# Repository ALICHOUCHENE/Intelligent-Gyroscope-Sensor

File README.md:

# Intelligent-Gyroscope-Sensor

Intelligent gyroscope sensor for Electronic stability control

Recognizing how a vehicle is steered and then alerting drivers in real time is of utmost importance to the vehicle and driver’s safety, since fatal accidents are often caused by dangerous vehicle maneuvers, such as rapid turns, fast lane-changes, etc.
In this paper, we make use of an intelligent sensor to take one step forward by developing a real-time accurate recognition system for dangerous vehicle steering maneuvers without the driver’s involvement. 
The basic idea is to use the sensor data to capture differences in the vehicle’s angular speed due to vehicle steering maneuvers, including turns, lane-changes and U-turns. 

 **Here the features of the Sensor :**

- STM32F103C8T6 ARM 32-bit Cortex™-M3 is the CPU of the board. Higher frequency, higher speed and cost-effictive.

- Gyroscope module, MPU6050, with I2C communication protocol. 

- CAN transeiver SN65HVD230

- SWD programming Interface.

- SPI for serial communication.

- USART for AT-commands mode in order to test the sensor before embedded it in the CAN bus.

- Voltage regulator with reverse voltage protection circuit.

**The schematic of the board :**

**The PCB layout of the board :**

**Board View :**

# Manufacturing : 

After finishing the Routing and verifying the pcb. We will make the board at JLC PCB and we chose also the PCB Assembly service.
Here is the BOM and posistion file needed to order from JLC PCB :

**BOM :**

| Designator | Value         | Footprint                                                 | LCSC Part |
|------------|---------------|-----------------------------------------------------------|-----------|
| C1         | 100nF         | Capacitor_SMD:C_0805_2012Metric_Pad1.15x1.40mm_HandSolder | C49678    |
| C2         | 10nF          | Capacitor_SMD:C_0402_1005Metric                           | C1525     |
| C3         | 100nF         | Capacitor_SMD:C_0402_1005Metric                           | C1525     |
| C4         | 100nF         | Capacitor_SMD:C_0402_1005Metric                           | C1525     |
| C5         | 100nF         | Capacitor_SMD:C_0402_1005Metric                           | C1525     |
| C6         | 100nF         | Capacitor_SMD:C_0402_1005Metric                           | C1525     |
| C7         | 100nF         | Capacitor_SMD:C_0402_1005Metric                           | C1525     |
| C8         | 100nF         | Capacitor_SMD:C_0402_1005Metric                           | C1525     |
| C12        | 100nF         | Capacitor_SMD:C_0402_1005Metric                           | C1525     |
| C13        | 100nF         | Capacitor_SMD:C_0402_1005Metric                           | C1525     |
| C15        | 100nF         | Capacitor_SMD:C_0402_1005Metric                           | C1525     |
| C16        | 100nF         | Capacitor_SMD:C_0402_1005Metric                           | C1525     |
| C9         | 4.7uF         | Capacitor_SMD:C_0402_1005Metric                           | C23733    |
| C10        | 4.7uF         | Capacitor_SMD:C_0402_1005Metric                           | C23733    |
| C11        | 4.7uF         | Capacitor_SMD:C_0402_1005Metric                           | C23733    |
| C14        | 2.2uF         | Capacitor_SMD:C_0402_1005Metric                           | C12530    |
| C17        | 470nF         | Capacitor_Tantalum_SMD:CP_EIA-2012-12_Kemet-R             |           |
| C18        | 22pF          | Capacitor_SMD:C_0402_1005Metric                           | C70464    |
| C19        | 22pF          | Capacitor_SMD:C_0402_1005Metric                           | C70464    |
| D1         | LED           | LED_SMD:LED_0402_1005Metric                               | C71911    |
| D2         | LED           | LED_SMD:LED_0402_1005Metric                               | C71911    |
| Q1         | AO3401A       | Package_TO_SOT_SMD:SOT-23                                 | C15127    |
| R1         | 4.7K          | Resistor_SMD:R_0402_1005Metric                            | C25900    |
| R2         | 4.7K          | Resistor_SMD:R_0402_1005Metric                            | C25900    |
| R3         | 100K          | Resistor_SMD:R_0402_1005Metric                            | C25741    |
| R4         | 1K            | Resistor_SMD:R_0402_1005Metric                            | C11702    |
| R5         | 1K            | Resistor_SMD:R_0402_1005Metric                            | C11702    |
| R6         | 10k           | Resistor_SMD:R_0402_1005Metric                            | C25744    |
| R7         | 1M            | Resistor_SMD:R_0402_1005Metric                            | C26083    |
| U1         | AMS1117-3.3   | Package_TO_SOT_SMD:SOT-223-3_TabPin2                      | C6186     |
| U2         | STM32F103C8Tx | Package_QFP:LQFP-48_7x7mm_P0.5mm                          | C8734     |
| U3         | MPU-6050      | Sensor_Motion:InvenSense_QFN-24_4x4mm_P0.5mm              | C24112    |
| U4         | SN65HVD230    | Package_SO:SOIC-8_3.9x4.9mm_P1.27mm                       | C12084    |
| Y1         | 8MHz          | Crystal:Crystal_SMD_0603-2Pin_6.0x3.5mm                   | C111120   |

**Position file :**

| Designator | Value         | Footprint                                   | Mid X      | Mid Y       | Rotation   | Layer |
|------------|---------------|---------------------------------------------|------------|-------------|------------|-------|
| C1         | 100nF         | C_0805_2012Metric_Pad1.15x1.40mm_HandSolder | 106.680000 | -76.708000  | 0.000000   | top   |
| C2         | 10nF          | C_0402_1005Metric                           | 105.156000 | -85.090000  | 0.000000   | top   |
| C3         | 100nF         | C_0402_1005Metric                           | 107.188000 | -85.344000  | 90.000000  | top   |
| C4         | 100nF         | C_0402_1005Metric                           | 119.126000 | -84.074000  | 180.000000 | top   |
| C5         | 100nF         | C_0402_1005Metric                           | 108.458000 | -85.344000  | 270.000000 | top   |
| C6         | 100nF         | C_0402_1005Metric                           | 120.142000 | -95.250000  | 90.000000  | top   |
| C7         | 100nF         | C_0402_1005Metric                           | 105.664000 | -95.758000  | 270.000000 | top   |
| C8         | 100nF         | C_0402_1005Metric                           | 119.126000 | -85.090000  | 180.000000 | top   |
| C9         | 4.7uF         | C_0402_1005Metric                           | 119.126000 | -95.250000  | 90.000000  | top   |
| C10        | 4.7uF         | C_0402_1005Metric                           | 104.648000 | -95.758000  | 270.000000 | top   |
| C11        | 4.7uF         | C_0402_1005Metric                           | 119.126000 | -86.106000  | 180.000000 | top   |
| C12        | 100nF         | C_0402_1005Metric                           | 100.584000 | -87.376000  | 90.000000  | top   |
| C13        | 100nF         | C_0402_1005Metric                           | 103.124000 | -85.090000  | 180.000000 | top   |
| C14        | 2.2uF         | C_0402_1005Metric                           | 102.616000 | -92.456000  | 180.000000 | top   |
| C15        | 100nF         | C_0402_1005Metric                           | 121.920000 | -95.250000  | 90.000000  | top   |
| C16        | 100nF         | C_0402_1005Metric                           | 107.188000 | -102.870000 | 180.000000 | top   |
| C17        | 470nF         | CP_EIA-2012-12_Kemet-R                      | 123.444000 | -74.422000  | 0.000000   | top   |
| C18        | 22pF          | C_0402_1005Metric                           | 116.586000 | -85.090000  | 0.000000   | top   |
| C19        | 22pF          | C_0402_1005Metric                           | 111.760000 | -85.090000  | 180.000000 | top   |
| D1         | LED           | LED_0402_1005Metric                         | 122.428000 | -93.218000  | 180.000000 | top   |
| D2         | LED           | LED_0402_1005Metric                         | 122.428000 | -92.202000  | 180.000000 | top   |
| Q1         | AO3401A       | SOT-23                                      | 106.680000 | -81.534000  | 270.000000 | top   |
| R1         | 4.7K          | R_0402_1005Metric                           | 105.664000 | -93.726000  | 90.000000  | top   |
| R2         | 4.7K          | R_0402_1005Metric                           | 104.648000 | -93.726000  | 90.000000  | top   |
| R3         | 100K          | R_0402_1005Metric                           | 105.156000 | -102.870000 | 0.000000   | top   |
| R4         | 1K            | R_0402_1005Metric                           | 120.396000 | -93.218000  | 180.000000 | top   |
| R5         | 1K            | R_0402_1005Metric                           | 120.396000 | -92.202000  | 180.000000 | top   |
| R6         | 10k           | R_0402_1005Metric                           | 122.936000 | -90.678000  | 90.000000  | top   |
| R7         | 1M            | R_0402_1005Metric                           | 114.554000 | -85.090000  | 180.000000 | top   |
| U1         | AMS1117-3.3   | SOT-223-3_TabPin2                           | 115.570000 | -76.708000  | 0.000000   | top   |
| U2         | STM32F103C8Tx | LQFP-48_7x7mm_P0.5mm                        | 114.046000 | -90.932000  | 270.000000 | top   |
| U3         | MPU-6050      | InvenSense_QFN-24_4x4mm_P0.5mm              | 103.886000 | -89.154000  | 180.000000 | top   |
| U4         | SN65HVD230    | SOIC-8_3.9x4.9mm_P1.27mm                    | 106.934000 | -99.568000  | 180.000000 | top   |
| Y1         | 8MHz          | Crystal_SMD_0603-2Pin_6.0x3.5mm             | 114.300000 | -82.550000  | 180.000000 | top   |

# Downloads

* [Board schematics](https://github.com/ALICHOUCHENE/Intelligent-Gyroscope-Sensor/blob/main/Schematics/Schematics.pdf)

* [BOM](https://github.com/ALICHOUCHENE/Intelligent-Gyroscope-Sensor/blob/main/Assembly/BOM.xlsx)

* [Position file](https://github.com/ALICHOUCHENE/Intelligent-Gyroscope-Sensor/blob/main/Assembly/Sensor-all-pos.xlsx)

* [Gerber File](https://github.com/ALICHOUCHENE/Intelligent-Gyroscope-Sensor/blob/main/GERBER/GERBER.rar)

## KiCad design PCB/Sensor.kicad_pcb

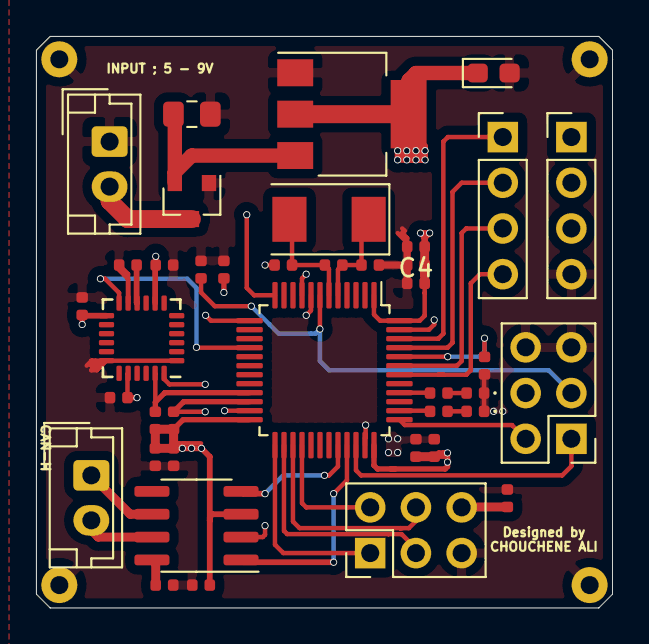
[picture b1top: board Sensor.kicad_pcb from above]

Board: 4 copper layers, 32.0 x 31.8 mm, 44 parts (0 on the bottom side), 34 nets.

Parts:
C1: 100nF; C_0805_2012Metric_Pad1.15x1.40mm_HandSolder
C2: 10nF; C_0402_1005Metric
C3, C4, C5, C6, C7, C8, C12, C13, C15, C16: 100nF; C_0402_1005Metric
C9, C10, C11: 4.7uF; C_0402_1005Metric
C14: 2.2uF; C_0402_1005Metric
C17: 470nF; CP_EIA-2012-12_Kemet-R
C18, C19: 22pF; C_0402_1005Metric
D1, D2: LED; LED_0402_1005Metric
H1, H2, H3, H4: GND; MountingHole_2.2mm_M2_DIN965_Pad
J1: Power Input; JST_EH_B2B-EH-A_1x02_P2.50mm_Vertical
J2: SWD; PinHeader_2x03_P2.54mm_Vertical
J3: USART2; PinHeader_1x04_P2.54mm_Vertical
J4: SPI; PinHeader_2x03_P2.54mm_Vertical
J5: GPIO; PinHeader_1x04_P2.54mm_Vertical
J6: CAN BUS; JST_EH_B2B-EH-A_1x02_P2.50mm_Vertical
Q1: AO3401A; SOT-23
R1, R2: 4.7K; R_0402_1005Metric
R3: 100K; R_0402_1005Metric
R4, R5: 1K; R_0402_1005Metric
R6: 10k; R_0402_1005Metric
R7: 1M; R_0402_1005Metric
U1: AMS1117-3.3; SOT-223-3_TabPin2
U2: STM32F103C8Tx; LQFP-48_7x7mm_P0.5mm
U3: MPU-6050; InvenSense_QFN-24_4x4mm_P0.5mm
U4: SN65HVD230; SOIC-8_3.9x4.9mm_P1.27mm
Y1: 8MHz; Crystal_SMD_0603-2Pin_6.0x3.5mm

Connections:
+9V: J1.2, Q1.3
BOOT: R6.2, U2.44
CAN_RX: U2.32, U4.4
CAN_TX: U2.33, U4.1
GND: C1.2, C2.2, C3.2, C4.2, C5.1, C6.2, C7.2, C8.2, C9.2, C10.2, C11.2, C12.2, C13.2, C14.2, C15.2, C16.2, C17.2, C18.2, C19.2, D1.1, D2.1, H1.1, H2.1, H3.1, H4.1, J1.1, J2.5, J2.6, J3.4, J4.5, Q1.1, R3.2, R6.1, U1.1, U2.8, U2.23, U2.35, U2.47, U3.1, U3.11, U3.18, U4.2
INT: U2.16, U3.12
IO0: J5.4, U2.42
IO1: J5.3, U2.43
IO2: J5.2, U2.45
IO3: J5.1, U2.46
MISO: J4.4, U2.27
MOSI: J4.2, U2.28
NRST: C3.1, J2.3, U2.7
unnamed: C1.1, Q1.2, U1.3
unnamed: C13.1, U3.10
unnamed: C14.1, U3.20
unnamed: D1.2, R4.1
unnamed: D2.2, R5.1
unnamed: J6.1, U4.6
unnamed: J6.2, U4.7
unnamed: R3.1, U4.8
PA15: R4.2, U2.38
PB4: R5.2, U2.40
SCK: J4.3, U2.26
SCL: R2.2, U2.21, U3.23
SDA: R1.2, U2.22, U3.24
SS: J4.1, U2.25
SWCLK: J2.2, U2.37
SWDIO: J2.1, U2.34
USART2_RX: J3.3, U2.13
USART2_TX: J3.2, U2.12
XTAL_IN: C18.1, R7.1, U2.5, Y1.1
XTAL_OUT: C19.1, R7.2, U2.6, Y1.2
v1: C2.1, C4.1, C5.2, C6.1, C7.1, C8.1, C9.1, C10.1, C11.1, C12.1, C15.1, C16.1, C17.1, J2.4, J3.1, J4.6, R1.1, R2.1, U1.2, U2.1, U2.9, U2.24, U2.36, U2.48, U3.8, U3.13, U4.3

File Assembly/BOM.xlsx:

Designator | Value | Footprint | LCSC Part
C1 | 100nF | Capacitor_SMD:C_0805_2012Metric_Pad1.15x1.40mm_HandSolder | C49678
C2 | 10nF | Capacitor_SMD:C_0402_1005Metric | C1525
C3 | 100nF | Capacitor_SMD:C_0402_1005Metric | C1525
C4 | 100nF | Capacitor_SMD:C_0402_1005Metric | C1525
C5 | 100nF | Capacitor_SMD:C_0402_1005Metric | C1525
C6 | 100nF | Capacitor_SMD:C_0402_1005Metric | C1525
C7 | 100nF | Capacitor_SMD:C_0402_1005Metric | C1525
C8 | 100nF | Capacitor_SMD:C_0402_1005Metric | C1525
C12 | 100nF | Capacitor_SMD:C_0402_1005Metric | C1525
C13 | 100nF | Capacitor_SMD:C_0402_1005Metric | C1525
C15 | 100nF | Capacitor_SMD:C_0402_1005Metric | C1525
C16 | 100nF | Capacitor_SMD:C_0402_1005Metric | C1525
C9 | 4.7uF | Capacitor_SMD:C_0402_1005Metric | C23733
C10 | 4.7uF | Capacitor_SMD:C_0402_1005Metric | C23733
C11 | 4.7uF | Capacitor_SMD:C_0402_1005Metric | C23733
C14 | 2.2uF | Capacitor_SMD:C_0402_1005Metric | C12530
C17 | 470nF | Capacitor_Tantalum_SMD:CP_EIA-2012-12_Kemet-R
C18 | 22pF | Capacitor_SMD:C_0402_1005Metric | C70464
C19 | 22pF | Capacitor_SMD:C_0402_1005Metric | C70464
D1 | LED | LED_SMD:LED_0402_1005Metric | C71911
D2 | LED | LED_SMD:LED_0402_1005Metric | C71911
Q1 | AO3401A | Package_TO_SOT_SMD:SOT-23 | C15127
R1 | 4.7K | Resistor_SMD:R_0402_1005Metric | C25900
R2 | 4.7K | Resistor_SMD:R_0402_1005Metric | C25900
R3 | 100K | Resistor_SMD:R_0402_1005Metric | C25741
R4 | 1K | Resistor_SMD:R_0402_1005Metric | C11702
R5 | 1K | Resistor_SMD:R_0402_1005Metric | C11702
R6 | 10k | Resistor_SMD:R_0402_1005Metric | C25744
R7 | 1M | Resistor_SMD:R_0402_1005Metric | C26083
U1 | AMS1117-3.3 | Package_TO_SOT_SMD:SOT-223-3_TabPin2 | C6186
U2 | STM32F103C8Tx | Package_QFP:LQFP-48_7x7mm_P0.5mm | C8734
U3 | MPU-6050 | Sensor_Motion:InvenSense_QFN-24_4x4mm_P0.5mm | C24112
U4 | SN65HVD230 | Package_SO:SOIC-8_3.9x4.9mm_P1.27mm | C12084
Y1 | 8MHz | Crystal:Crystal_SMD_0603-2Pin_6.0x3.5mm | C111120
